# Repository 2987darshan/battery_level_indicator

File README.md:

# BATTERY LEVEL INDICATOR
## Overview
-A simple PCB design for battery level indicator circuit using LED's
## Tools used
-KiCad
## Features
-It gives a battery level indication.
-The LED named FULL glows when the battery is charged 
-The LOW glows when the battery is discharged.
## Limitations
-This is my frist step towards PCB designing and it works well for 9V battery but when the voltage of battery changes or the battery changes,it might not work as expected especially for low voltage cells like a AA battery of 1.5V and for higher voltages like 12V.
## Future refinements
-improving the circuit so that even batteries of different voltages (0-25V) can be tested with the same circuit.(not very accurate).
## Status
Designed and tested on a breadboard

## 3D View

## PCB Layout

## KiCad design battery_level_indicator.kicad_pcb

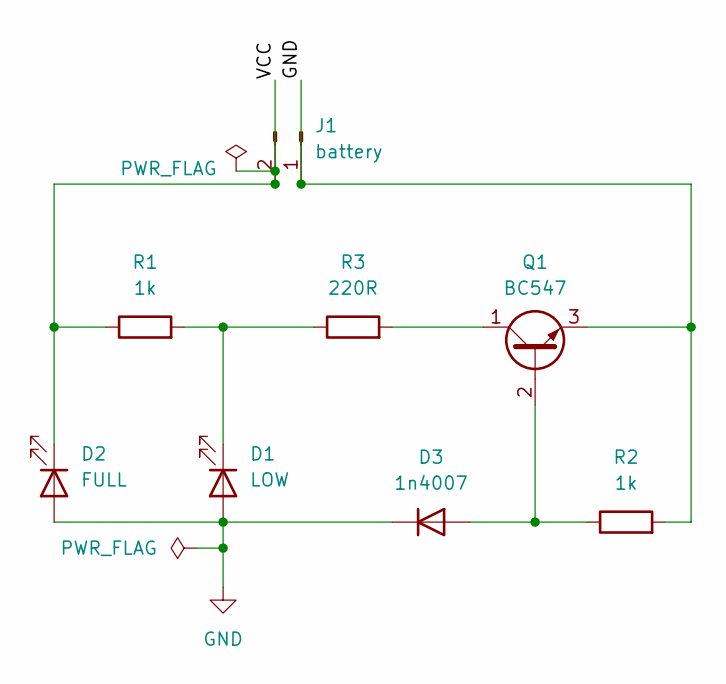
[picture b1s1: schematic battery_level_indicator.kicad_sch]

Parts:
D1: LOW; LED_D5.0mm
D2: FULL; LED_D5.0mm
D3: 1n4007; D_DO-41_SOD81_P7.62mm_Horizontal
J1: battery; TerminalBlock_MaiXu_MX126-5.0-02P_1x02_P5.00mm
Q1: BC547; TO-92_Inline
R1, R2: 1k; R_Axial_DIN0207_L6.3mm_D2.5mm_P7.62mm_Horizontal
R3: 220R; R_Axial_DIN0207_L6.3mm_D2.5mm_P7.62mm_Horizontal

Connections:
GND: D1.2 (A), D2.2 (A), D3.1 (K)
unnamed: D1.1 (K), R1.2, R3.1
unnamed: D2.1 (K), J1.2, R1.1
unnamed: D3.2 (A), Q1.2 (B), R2.1
unnamed: J1.1, Q1.3 (E), R2.2
unnamed: Q1.1 (C), R3.2

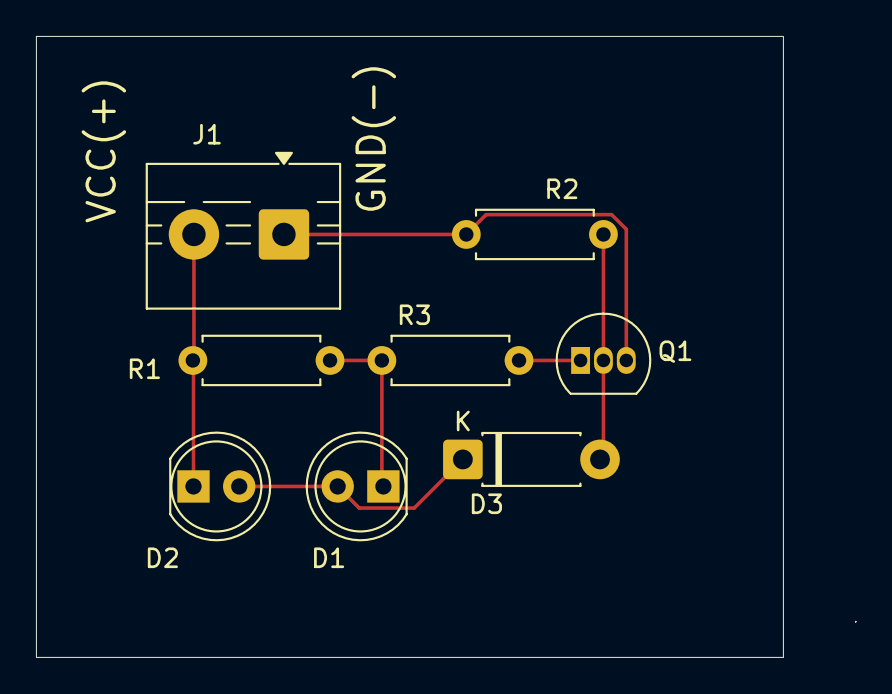
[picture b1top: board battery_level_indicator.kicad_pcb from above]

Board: 2 copper layers, 45.5 x 34.5 mm, 8 parts (0 on the bottom side), 6 nets.

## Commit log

2026-03-24 Rename battery level indicator pcb layout.jpeg to pcb_layout.jpeg
2026-03-24 Rename battery level indicator 3d.jpeg to 3d_view.jpeg
